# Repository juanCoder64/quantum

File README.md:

# quantum
todo lo que tenga que ver con el equipo de TMR
tal como pruebas de partes del robot, como va el codigo final y si se puede el diseño

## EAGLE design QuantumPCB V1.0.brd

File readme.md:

# ejemplos
 ## [brujula](https://github.com/juanCoder64/quantum/tree/master/Ejemplos/brujula)
### Que hace
 Orienta el robot hacia el lugar donde empezó
### librerías necesarias
 * [Movimiento](https://github.com/juanCoder64/quantum/tree/master/Bibliotecas/Movimiento)
 * Wire
 * Adafruit_Sensor
 * Adafruit_BNO055
 * Adafruit_GFX
 * Adafruit_SSD1306
 ## [buscar_pelota](https://github.com/juanCoder64/quantum/tree/master/Ejemplos/buscar_pelota)
  ### Que hace
   Busca la pelota usando los sensores IR y luego la sigue.
  ### librerías necesarias:
   * [IR360](https://github.com/juanCoder64/quantum/tree/master/Bibliotecas/IR360)
   * Wire
   * Adafruit_Sensor
   * Adafruit_BNO055
   * Adafruit_SSD1306
   * Adafruit_GFX
   * HTInfraredSeeker
   * [Movimiento](https://github.com/juanCoder64/quantum/tree/master/Bibliotecas/Movimiento)

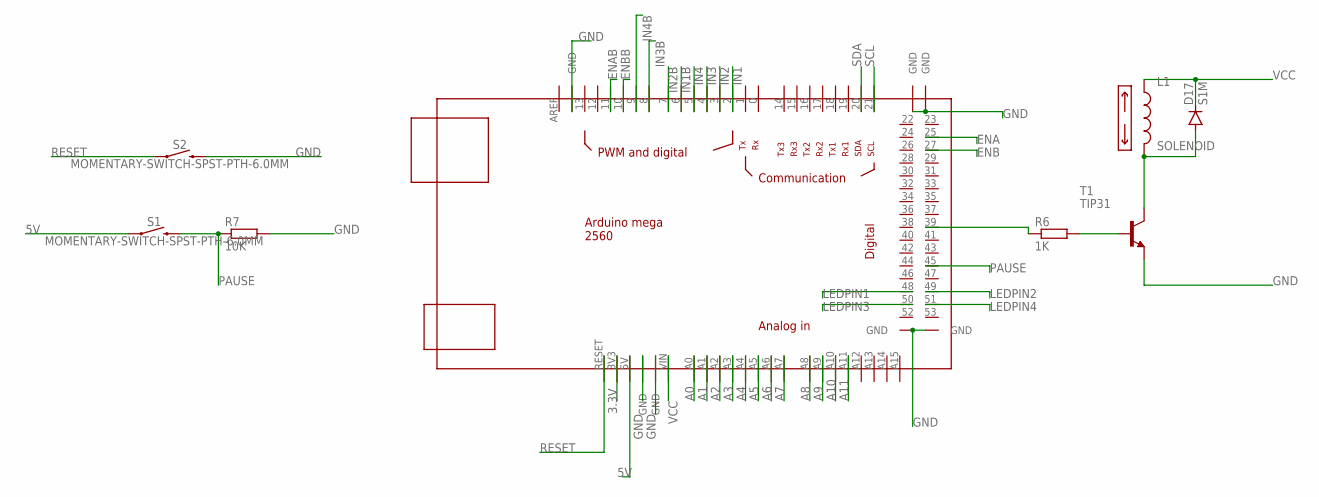
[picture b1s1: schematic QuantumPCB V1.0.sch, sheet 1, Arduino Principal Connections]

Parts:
D17: S1M; SMA
L1: SOLENOID; 1X02
R6: 1K; R0603
R7: 10K; R0603
S1, S2: MOMENTARY-SWITCH-SPST-PTH-6.0MM; TACTILE_SWITCH_PTH_6.0MM
T1: TIP31; TO220
U$1: MEGA_DEVICE; MEGAOUTLINE

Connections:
3.3V: U$1.3V3; also elsewhere on the board
5V: S1.1, U$1.5V; also elsewhere on the board
A0: U$1.A0; also elsewhere on the board
A1: U$1.A1; also elsewhere on the board
A2: U$1.A2; also elsewhere on the board
A3: U$1.A3; also elsewhere on the board
A4: U$1.A4; also elsewhere on the board
A5: U$1.A5; also elsewhere on the board
A6: U$1.A6; also elsewhere on the board
A7: U$1.A7; also elsewhere on the board
A8: U$1.A8; also elsewhere on the board
A9: U$1.A9; also elsewhere on the board
A10: U$1.A10; also elsewhere on the board
A11: U$1.A11; also elsewhere on the board
ENA: U$1.25; also elsewhere on the board
ENAB: U$1.11; also elsewhere on the board
ENB: U$1.27; also elsewhere on the board
ENBB: U$1.10; also elsewhere on the board
GND: R7.2, S2.3 (2), T1.3 (E), U$1.GND@1 (GND), U$1.GND@2 (GND), U$1.GND@3 (GND), U$1.GND@4 (GND), U$1.GND@5 (GND), U$1.GND@6 (GND), U$1.GND@7 (GND); also elsewhere on the board
IN1: U$1.2; also elsewhere on the board
IN1B: U$1.6; also elsewhere on the board
IN2: U$1.3; also elsewhere on the board
IN2B: U$1.7; also elsewhere on the board
IN3: U$1.4; also elsewhere on the board
IN3B: U$1.8; also elsewhere on the board
IN4: U$1.5; also elsewhere on the board
IN4B: U$1.9; also elsewhere on the board
LEDPIN1: U$1.48; also elsewhere on the board
LEDPIN2: U$1.49; also elsewhere on the board
LEDPIN3: U$1.50; also elsewhere on the board
LEDPIN4: U$1.51; also elsewhere on the board
unnamed: R6.1, U$1.39
unnamed: R6.2, T1.1 (B)
unnamed: D17.A, L1.2, T1.2 (C)
PAUSE: R7.1, S1.3 (2), U$1.45
RESET: S2.1, U$1.RESET
SCL: U$1.21; also elsewhere on the board
SDA: U$1.20; also elsewhere on the board
VCC: D17.C, L1.1, U$1.VIN; also elsewhere on the board

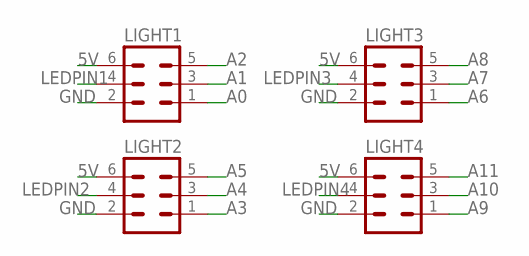
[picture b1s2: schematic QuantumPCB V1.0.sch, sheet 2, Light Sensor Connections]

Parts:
LIGHT1, LIGHT2, LIGHT3, LIGHT4: MA03-2

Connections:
5V: LIGHT1.6, LIGHT2.6, LIGHT3.6, LIGHT4.6; also elsewhere on the board
A0: LIGHT1.1; also elsewhere on the board
A1: LIGHT1.3; also elsewhere on the board
A2: LIGHT1.5; also elsewhere on the board
A3: LIGHT2.1; also elsewhere on the board
A4: LIGHT2.3; also elsewhere on the board
A5: LIGHT2.5; also elsewhere on the board
A6: LIGHT3.1; also elsewhere on the board
A7: LIGHT3.3; also elsewhere on the board
A8: LIGHT3.5; also elsewhere on the board
A9: LIGHT4.1; also elsewhere on the board
A10: LIGHT4.3; also elsewhere on the board
A11: LIGHT4.5; also elsewhere on the board
GND: LIGHT1.2, LIGHT2.2, LIGHT3.2, LIGHT4.2; also elsewhere on the board
LEDPIN1: LIGHT1.4; also elsewhere on the board
LEDPIN2: LIGHT2.4; also elsewhere on the board
LEDPIN3: LIGHT3.4; also elsewhere on the board
LEDPIN4: LIGHT4.4; also elsewhere on the board

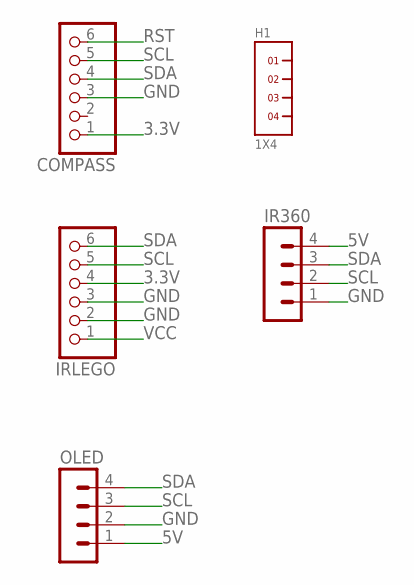
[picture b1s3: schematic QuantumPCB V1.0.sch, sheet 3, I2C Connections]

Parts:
COMPASS: PINHD-1X6; 1X06
H1: 1X4
IR360: MA04-1
IRLEGO: PINHD-1X6; 1X06
OLED: MA04-1

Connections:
3.3V: COMPASS.1, IRLEGO.4; also elsewhere on the board
5V: IR360.4, OLED.1; also elsewhere on the board
GND: COMPASS.3, IR360.1, IRLEGO.2, IRLEGO.3, OLED.2; also elsewhere on the board
RST: COMPASS.6
SCL: COMPASS.5, IR360.2, IRLEGO.5, OLED.3; also elsewhere on the board
SDA: COMPASS.4, IR360.3, IRLEGO.6, OLED.4; also elsewhere on the board
VCC: IRLEGO.1; also elsewhere on the board

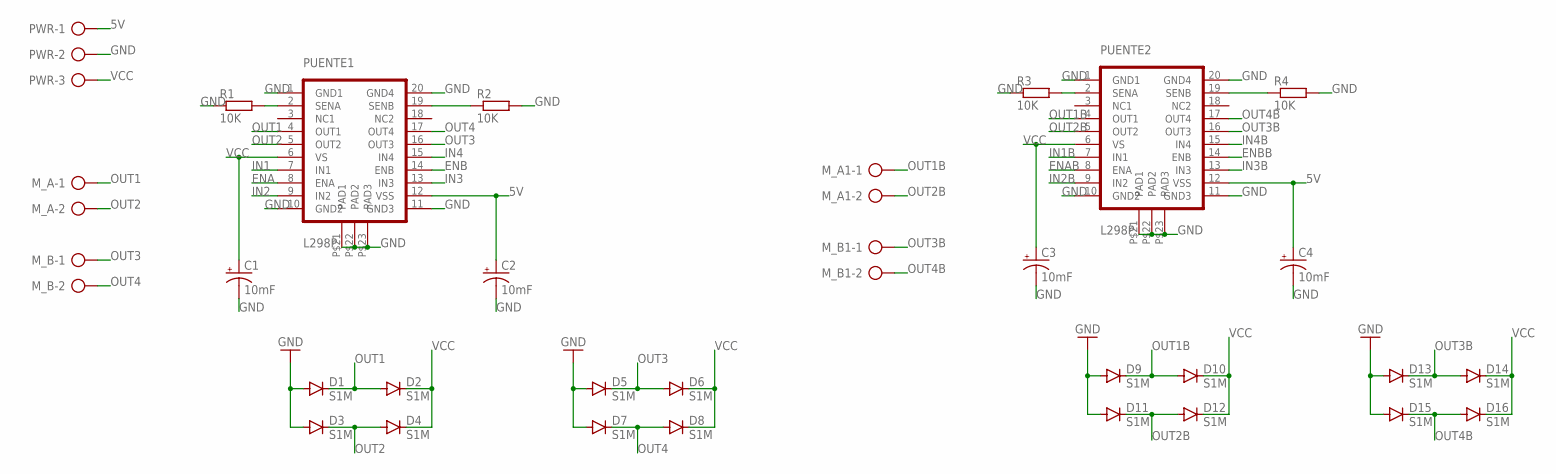
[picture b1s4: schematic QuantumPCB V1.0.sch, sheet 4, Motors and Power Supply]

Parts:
C1, C2, C3, C4: 10mF; E2-5
D1, D2, D3, D4, D5, D6, D7, D8, D9, D10, D11, D12, D13, D14, D15, D16: S1M; SMA
M_A, M_A1: AK500/2
M_B, M_B1: AK500/2
PUENTE1, PUENTE2: L298P; POWER-SO20
PWR: AK500/3
R1, R2, R3, R4: 10K; R0603

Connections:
5V: C2.+, C4.+, PUENTE1.P$12 (VSS), PUENTE2.P$12 (VSS), PWR.1; also elsewhere on the board
ENA: PUENTE1.P$8 (ENA); also elsewhere on the board
ENAB: PUENTE2.P$8 (ENA); also elsewhere on the board
ENB: PUENTE1.P$14 (ENB); also elsewhere on the board
ENBB: PUENTE2.P$14 (ENB); also elsewhere on the board
GND: C1.-, C2.-, C3.-, C4.-, D1.A, D3.A, D5.A, D7.A, D9.A, D11.A, D13.A, D15.A, PUENTE1.P$1 (GND1), PUENTE1.P$10 (GND2), PUENTE1.P$11 (GND3), PUENTE1.P$20 (GND4), PUENTE1.P$21 (PAD1), PUENTE1.P$22 (PAD2), PUENTE1.P$23 (PAD3), PUENTE2.P$1 (GND1), PUENTE2.P$10 (GND2), PUENTE2.P$11 (GND3), PUENTE2.P$20 (GND4), PUENTE2.P$21 (PAD1), PUENTE2.P$22 (PAD2), PUENTE2.P$23 (PAD3), PWR.2, R1.1, R2.2, R3.1, R4.2; also elsewhere on the board
IN1: PUENTE1.P$7 (IN1); also elsewhere on the board
IN1B: PUENTE2.P$7 (IN1); also elsewhere on the board
IN2: PUENTE1.P$9 (IN2); also elsewhere on the board
IN2B: PUENTE2.P$9 (IN2); also elsewhere on the board
IN3: PUENTE1.P$13 (IN3); also elsewhere on the board
IN3B: PUENTE2.P$13 (IN3); also elsewhere on the board
IN4: PUENTE1.P$15 (IN4); also elsewhere on the board
IN4B: PUENTE2.P$15 (IN4); also elsewhere on the board
unnamed: PUENTE1.P$2 (SENA), R1.2
unnamed: PUENTE1.P$19 (SENB), R2.1
unnamed: PUENTE2.P$2 (SENA), R3.2
unnamed: PUENTE2.P$19 (SENB), R4.1
OUT1: D1.C, D2.A, M_A.1, PUENTE1.P$4 (OUT1)
OUT1B: D9.C, D10.A, M_A1.1, PUENTE2.P$4 (OUT1)
OUT2: D3.C, D4.A, M_A.2, PUENTE1.P$5 (OUT2)
OUT2B: D11.C, D12.A, M_A1.2, PUENTE2.P$5 (OUT2)
OUT3: D5.C, D6.A, M_B.1, PUENTE1.P$16 (OUT3)
OUT3B: D13.C, D14.A, M_B1.1, PUENTE2.P$16 (OUT3)
OUT4: D7.C, D8.A, M_B.2, PUENTE1.P$17 (OUT4)
OUT4B: D15.C, D16.A, M_B1.2, PUENTE2.P$17 (OUT4)
VCC: C1.+, C3.+, D2.C, D4.C, D6.C, D8.C, D10.C, D12.C, D14.C, D16.C, PUENTE1.P$6 (VS), PUENTE2.P$6 (VS), PWR.3; also elsewhere on the board

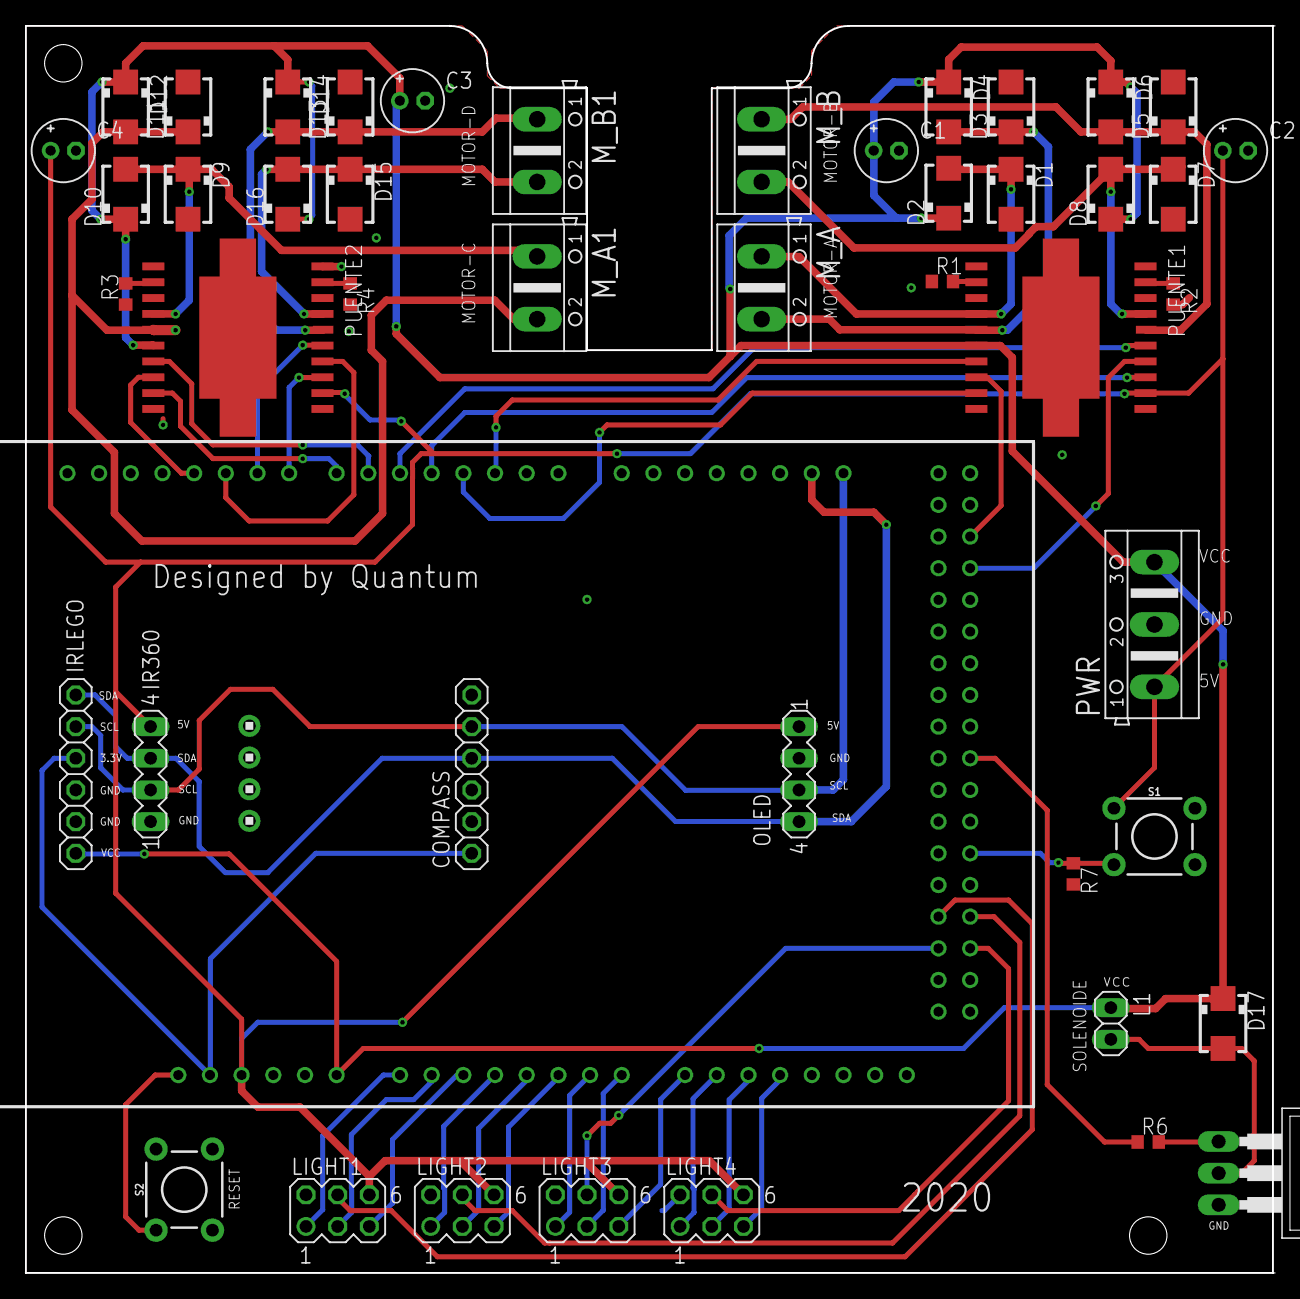
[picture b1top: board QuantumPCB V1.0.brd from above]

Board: 2 copper layers, 100.1 x 100.0 mm, 48 parts (0 on the bottom side), 51 nets.

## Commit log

2019-09-01 Rename la_progra.ino to la_prograF.ino
2019-09-01 Create readme.md
    aqui va todo lo que llevamos
2019-09-05 add new
2019-09-06 5/09/19
2019-09-07 optimizar calibración
2019-09-07 cambios
2019-09-07 orientacion
2019-09-17 quantum -[:]
2019-09-19 arreglar el bug de la calibración
2019-09-28 agregar nueva librería ya arreglada
2019-10-12 programación
2019-11-12 algunos cambios son experimentales
2019-11-12 fixed bugs!
2019-11-12 arreglos
2019-11-12 chaBots -[:] Quantum֍
2019-11-12 Auto stash before rebase of "refs/heads/master"
2019-11-12 Chabots Quantum -[:]
    -[:]
2019-11-17 Chabots Quenatum -[:]
2019-11-18 velocista
2019-11-18 versión 2.0
    se añaden motores
2019-12-04 sensor color
2019-12-22 mejoras en librería
    en la vuelta solo tiene proporcional
2019-12-27 corrección PID
2020-01-19 libreria360
2020-01-19 libreria_Linea
2020-01-19 Quantum
2020-01-19 Linea
2020-02-16 reparacion de libreria de moviniemto
2020-03-01 enable pins
2020-03-01 comentarios
2020-03-01 añadir pruebas
2020-03-08 agregar.zip
2020-03-08 seguir la pelota con los 2 sensores
2020-03-08 actualizar todo
2020-03-08 Ruedas
2020-03-13 codigo final
2020-03-13 OLED
2020-06-03 algoritmos nuevos
2020-07-05 orden
2020-07-05 autodiagnostico

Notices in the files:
parts and their libraries:
SparkFun-Switches: Licensing: Creative Commons ShareAlike 4.0 International - https://creativecommons.org/licenses/by-sa/4.0
